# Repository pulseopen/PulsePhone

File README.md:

# PulsePhone — Pulse Modular Phone (DART-MX8M-MINI SoM)

> A modular, open-source smartphone built for repairability, upgradability, and hardware freedom.

Built around the **DART-MX8M-MINI SoM**, PulsePhone uses **Hirose DF40** board-to-board connectors across all subsystems — keeping modules isolated, swappable, and independently developable.

---

## Sponsorship
PulsePhone is proudly sponsored by [PCBWay](https://www.pcbway.com), 
through their project sponsorship program.

---

## System Architecture

The **Main Board** is the hub of the system, hosting the MCM-iMX93 SoM, power management, WiFi/BT, onboard DAC, and all signal routing. Every peripheral connects via DF40 connectors following the MBI-Lite standard.

| Module         | Interface          | Role                                               |
|----------------|--------------------|----------------------------------------------------|
| Main Board     | DF40 (host)        | MCM-iMX93 SoM, WiFi/BT, DAC, power management     |
| Display Module | MIPI-DSI + Touch   | Adapter for wide MIPI-DSI display compatibility    |
| Camera Module  | MIPI CSI-2         | Adapter for wide MIPI-CSI camera compatibility     |
| Audio Module   | Analog             | Amp, speaker, headphone, mic                       |

Full connector pinout in [MBI-Lite Specification](MBI-LITE.md).

---

## Project Goals

- One connector standard (DF40) across every module
- Debian
- Kit-oriented design — bring your own display and case
- Fully open: KiCad source + mechanical files under GNU GPL-V3.0

---

## Hardware Status

### Main Board — Rev 2
- DART-MX8M-MINI
- M.2 WiFi/BT Module.
- PCM5102A audio DAC routed to SAI port
- TPS63020 buck-boost regulator, AP2112K-3.3 LDO
- TP4056 battery charger, MIC2877 5V boost

### Rev 1 — Lessons Learned
- XL1509 EN pin active-low behavior caused 3.3V rail failure (fixed in Rev 2 by switching to AP2112K LDO)
- Test pad size too small for reliable probing (all pads 2mm minimum in Rev 2)
- SoM partial boot activity observed but UART output not confirmed **More on this below*

### Display Module
PCB design complete. Functions as a passive MIPI-DSI adapter for broad display compatibility.

### Camera Module
Design TBD.

### Audio Module
Design in progress.

### Wifi/BT (M.2 Module)
M.2 key e connector which allows for a wide range of consumer wifi solutions.

### Mod Port (NEW DF40 MODULE!)
New connector that allows tinkerers to make their own custom pulsephone modules (ex. custom rfid modules, ir remote module, etc...)! Connector's pinout is stocked with loads of GPIO, UART, and I2C.

---

## Software Target

- **OS:** Debian linux
- **Target:** First Linux boot soon...

---

## First Bringup Summary (Rev 1) *Failed :(*

- First bringup was not a success as boot only got upto flashing light on the SoM.
- Soldering is to be improved upon with planned access to a Uni FabLab.
- I presume the main cause for failure of Rev 1 was poor soldering quality and electrical faults that were not caught before ordering boards.

---

## Current Status

Rev 2 schematic and PCB complete. Pre-order review week in progress before board order. Targeting first Linux boot on Rev 2 hardware.

---

## Documentation

- [MBI-Lite Module Connector Specification](MBI-LITE.md)
- [Contributing](CONTRIBUTING.md)
- [License](LICENSE)

---

## License

Hardware released under **GNU GPL-V3.0**.

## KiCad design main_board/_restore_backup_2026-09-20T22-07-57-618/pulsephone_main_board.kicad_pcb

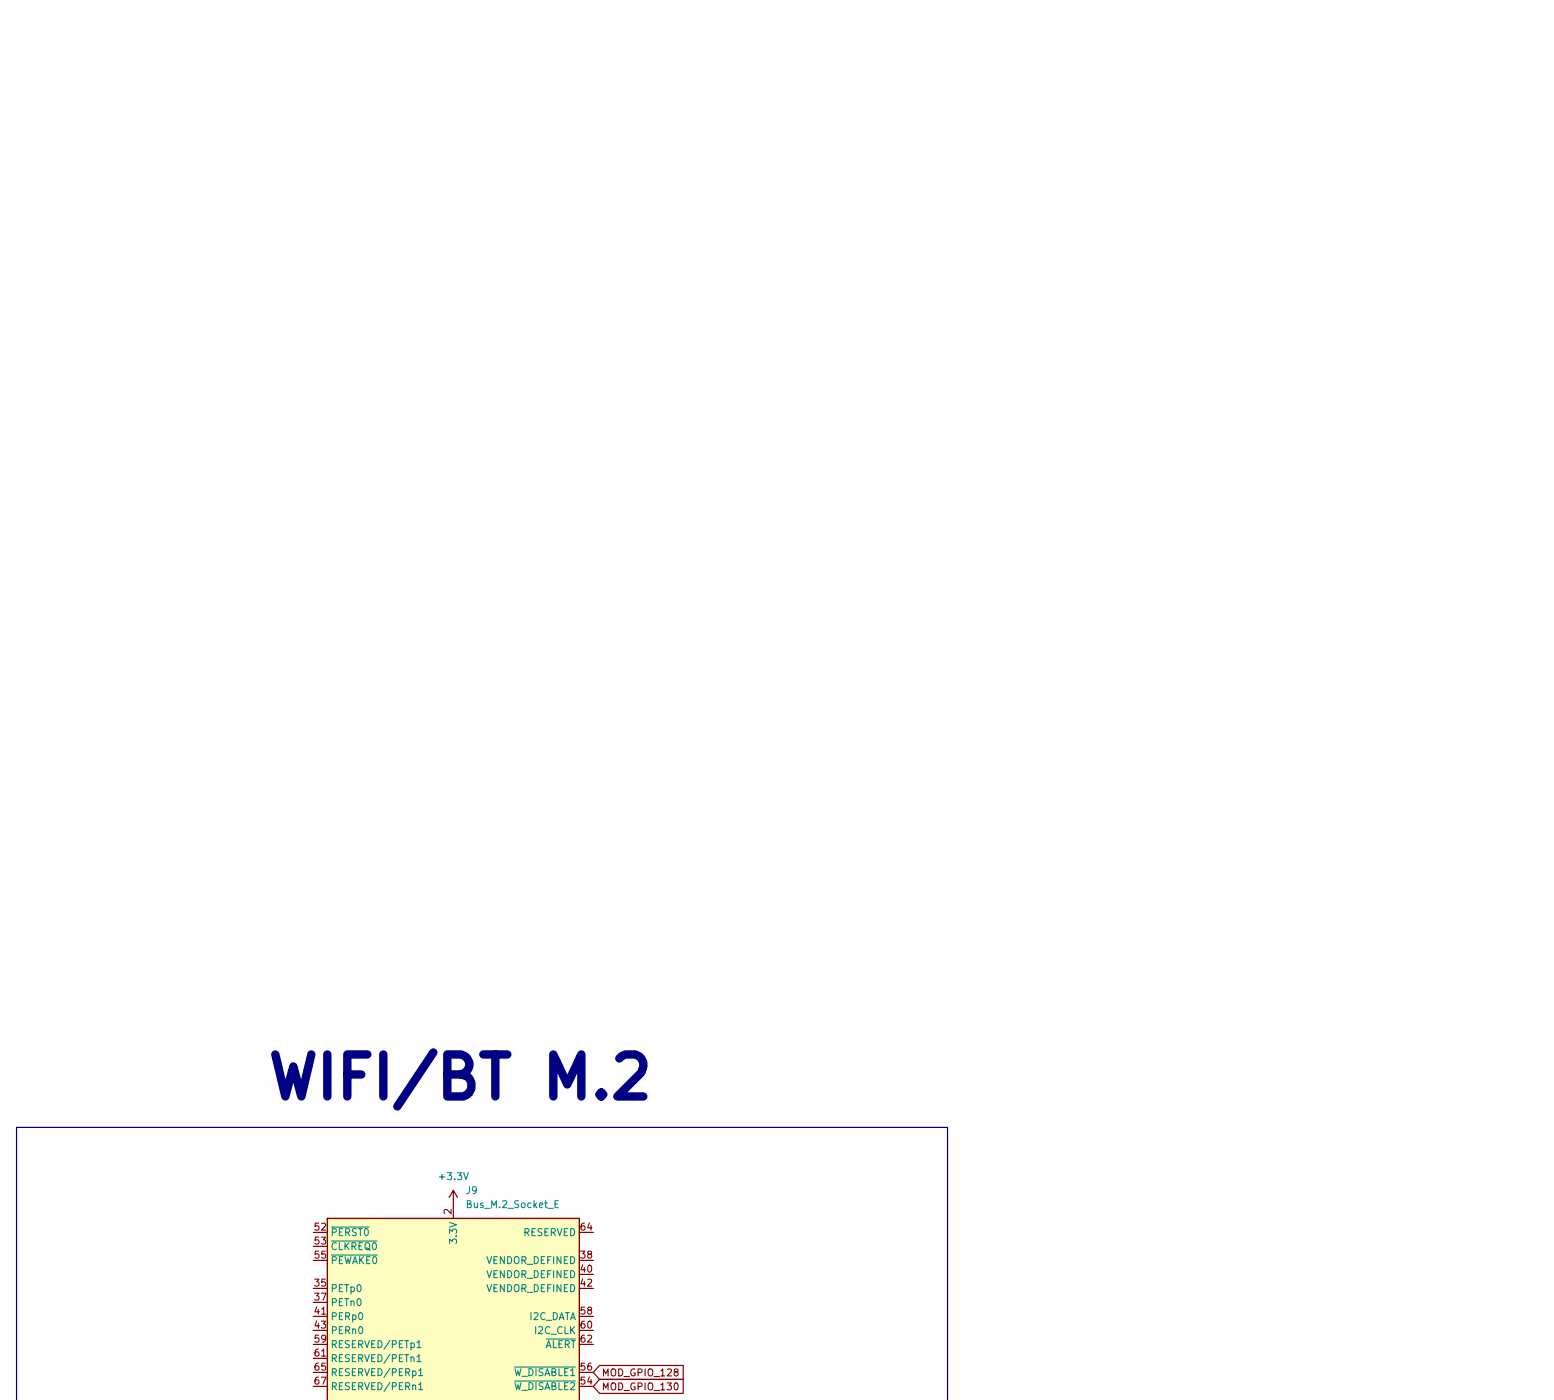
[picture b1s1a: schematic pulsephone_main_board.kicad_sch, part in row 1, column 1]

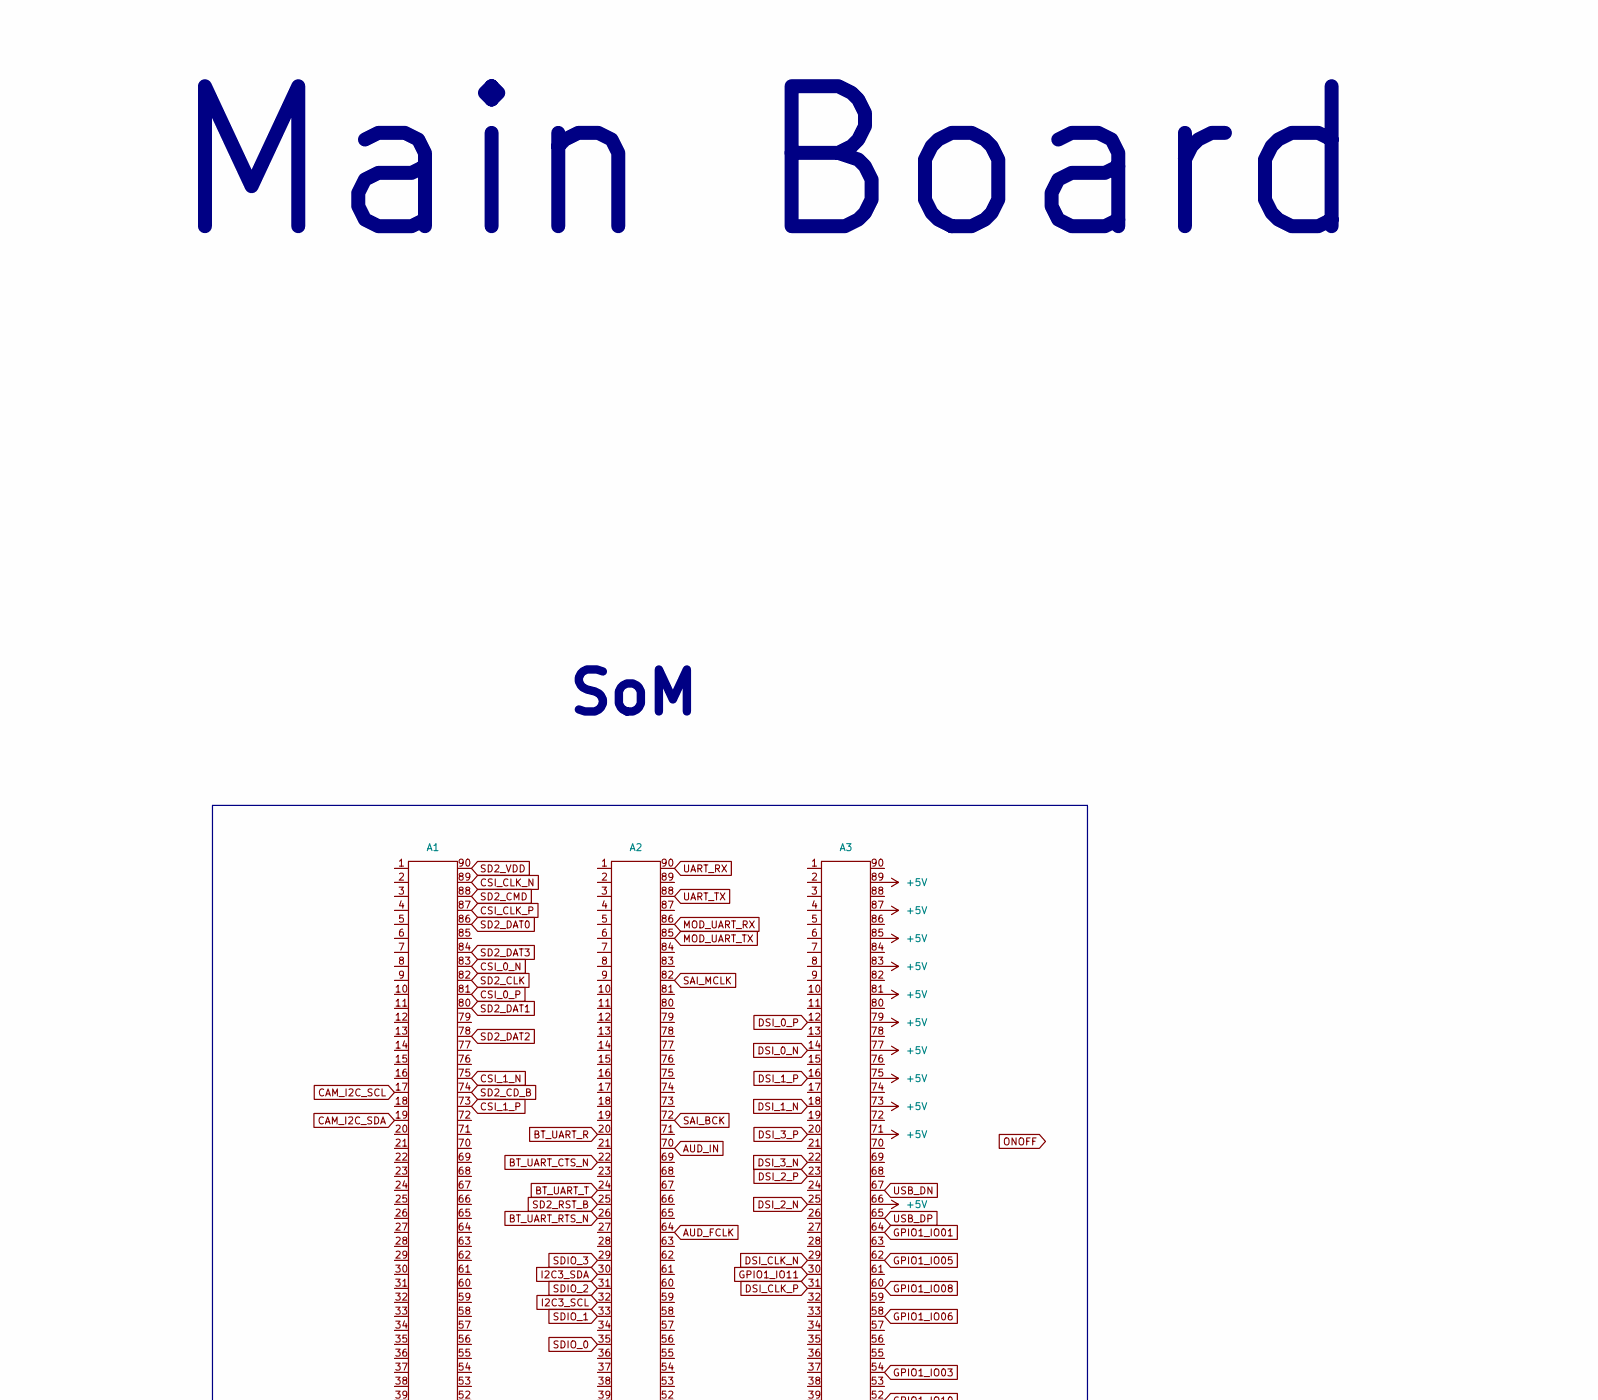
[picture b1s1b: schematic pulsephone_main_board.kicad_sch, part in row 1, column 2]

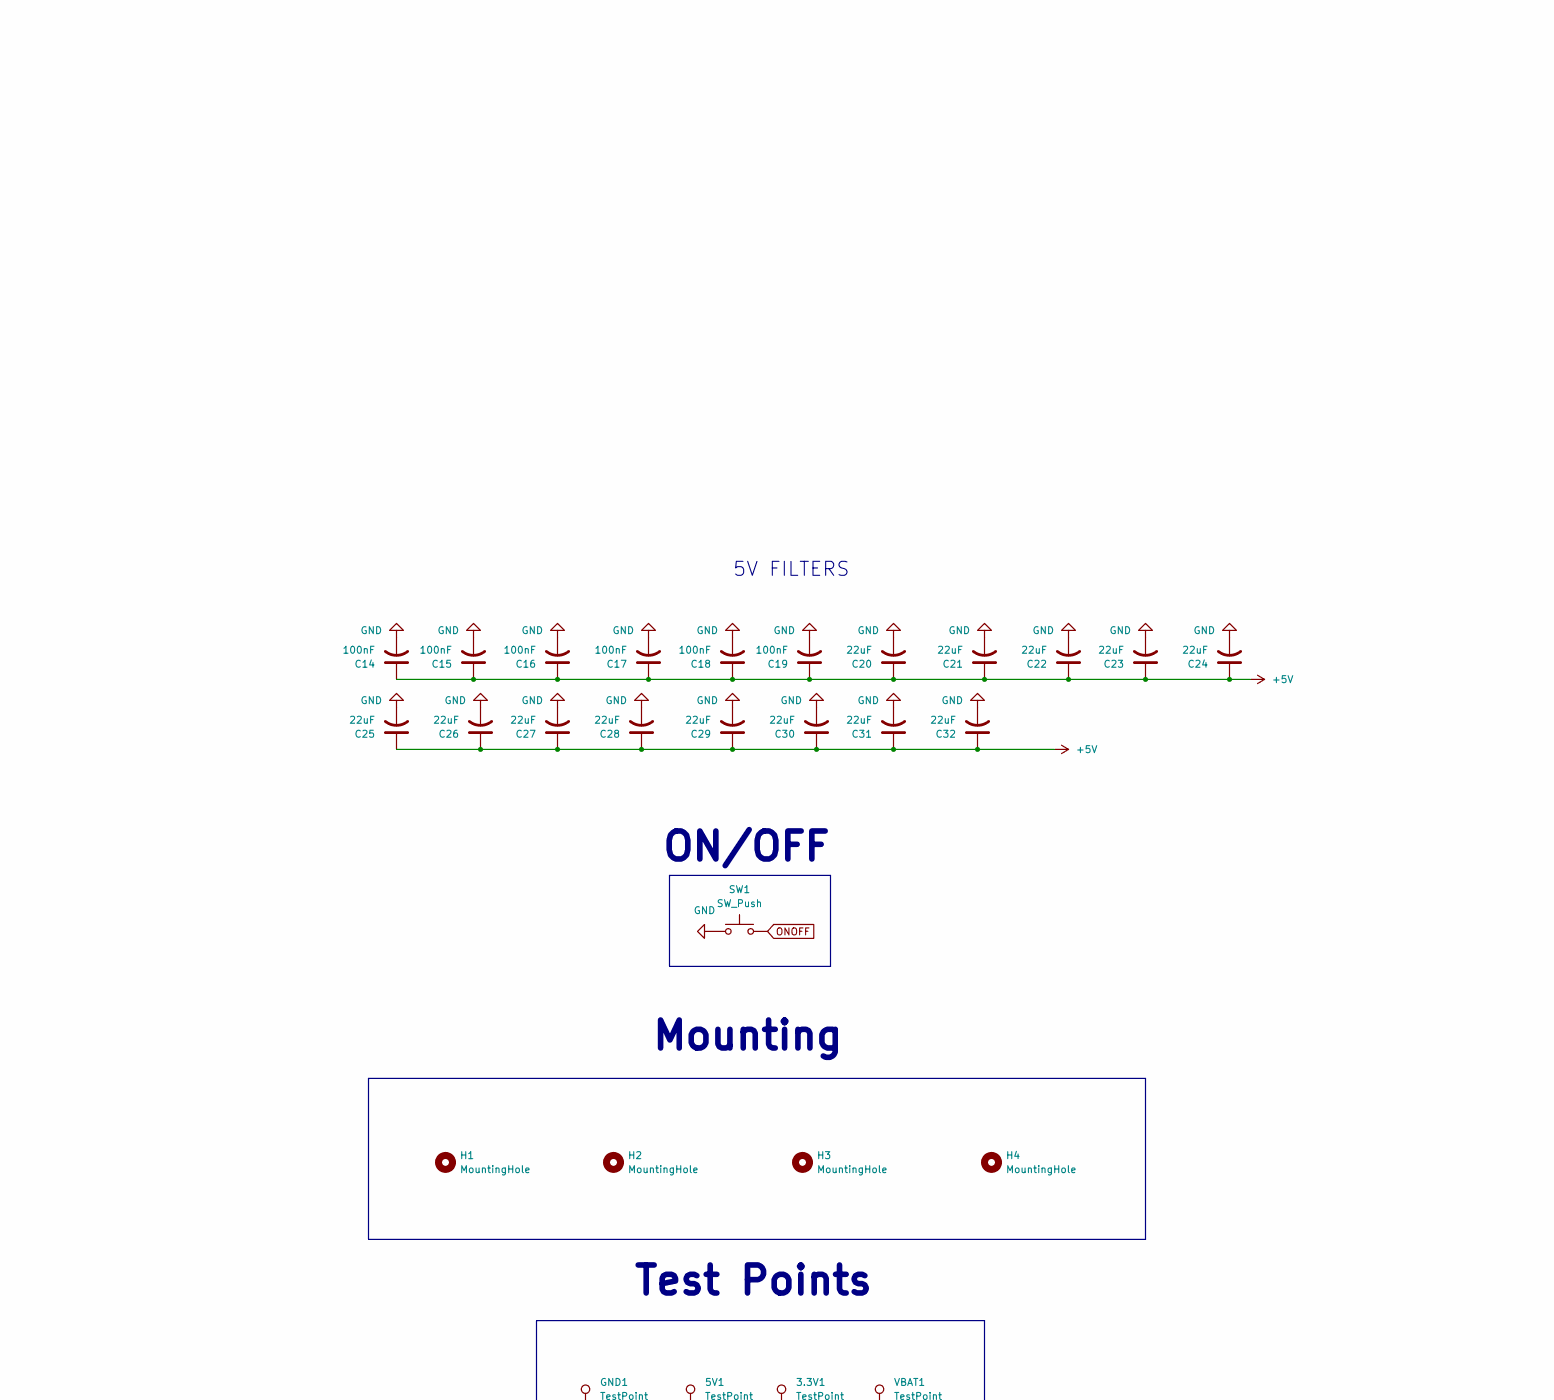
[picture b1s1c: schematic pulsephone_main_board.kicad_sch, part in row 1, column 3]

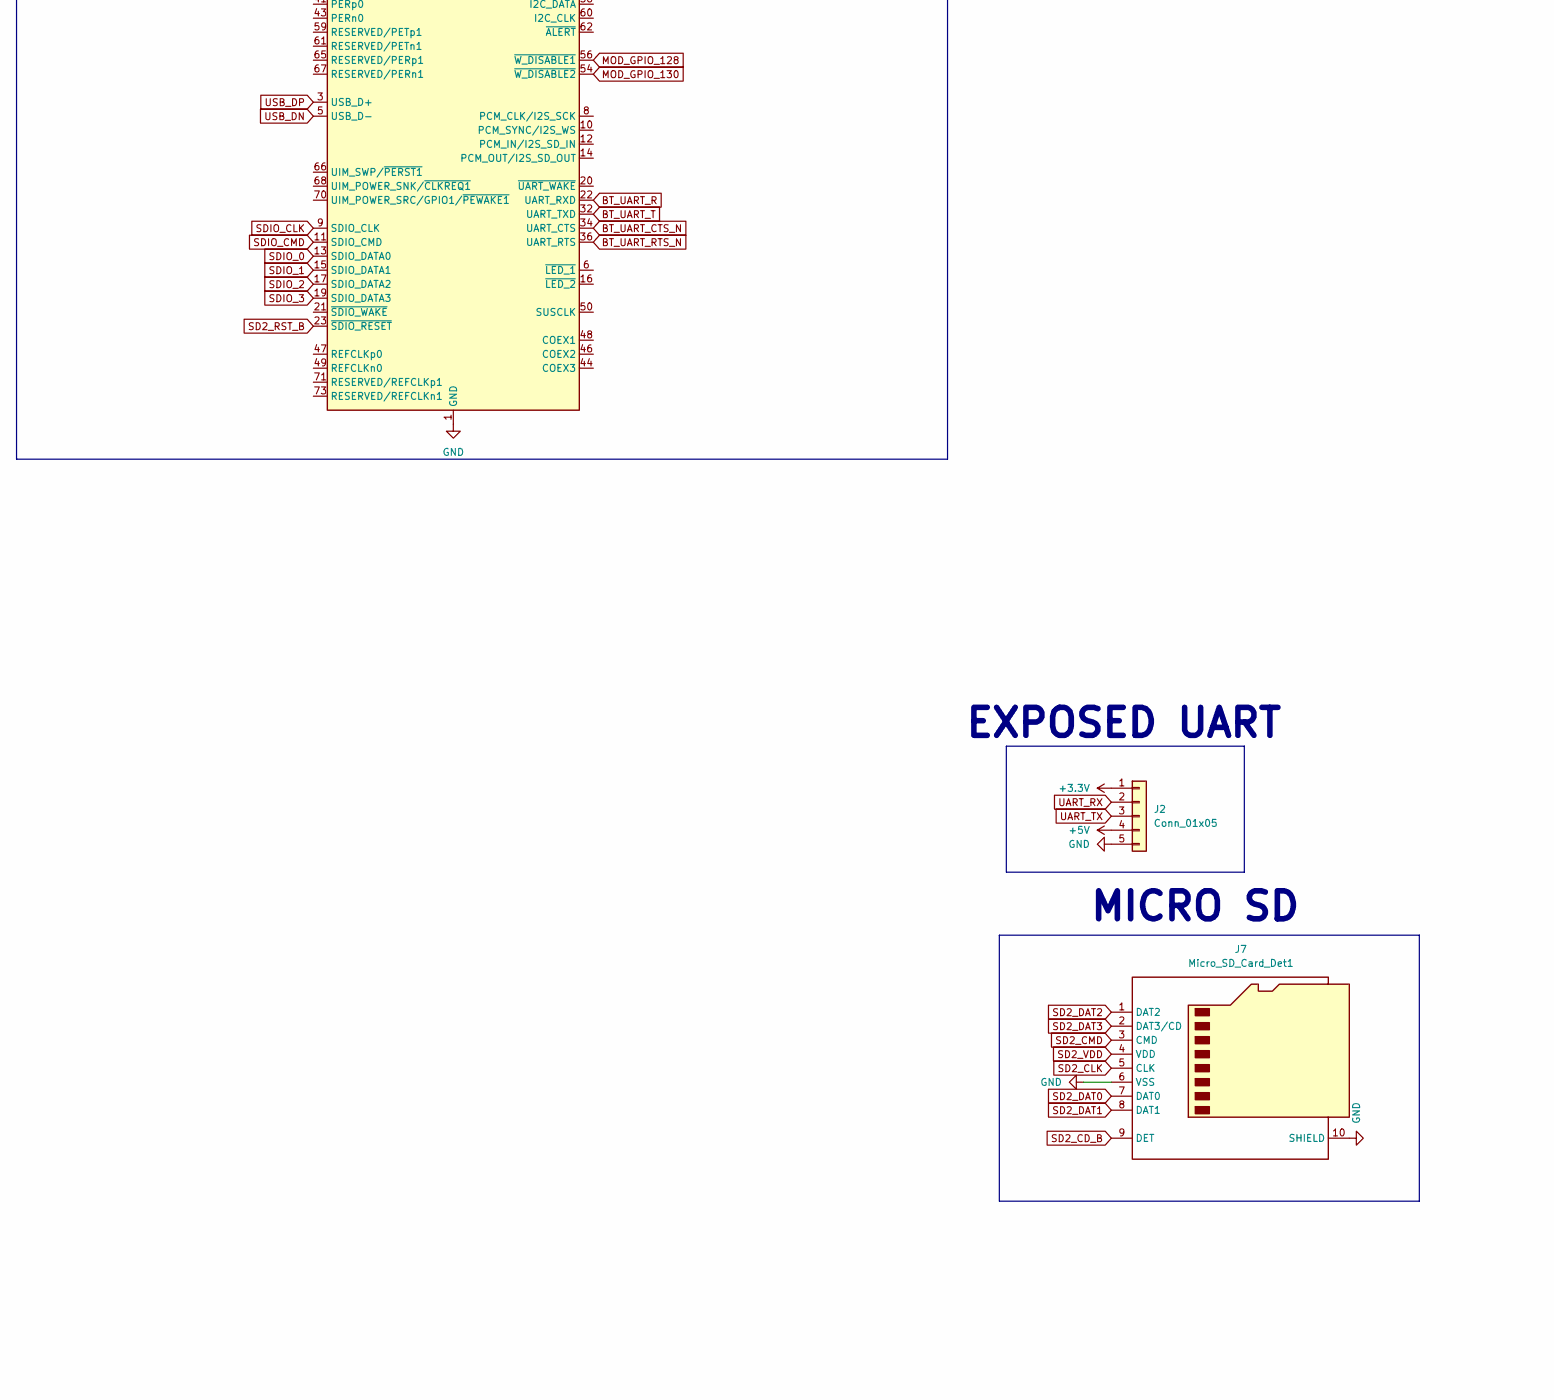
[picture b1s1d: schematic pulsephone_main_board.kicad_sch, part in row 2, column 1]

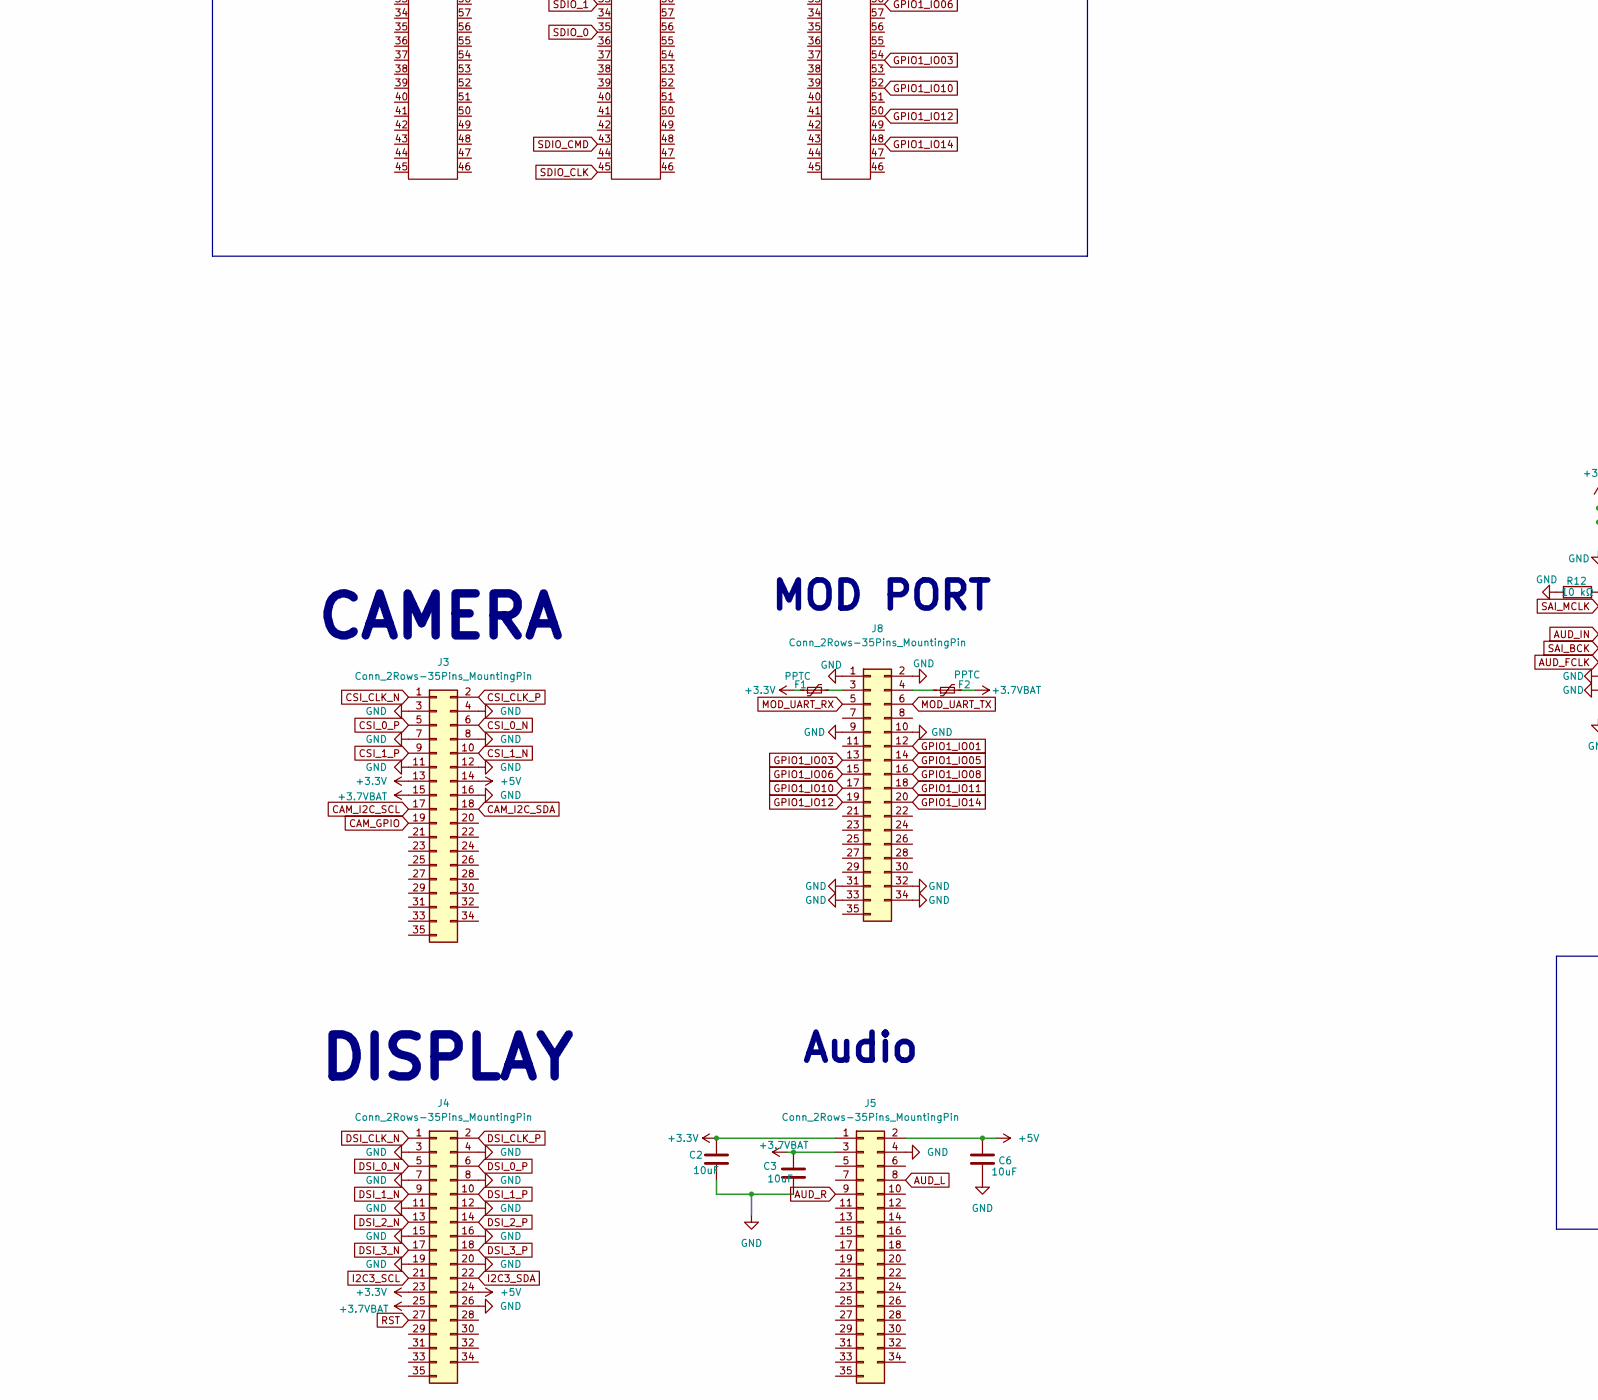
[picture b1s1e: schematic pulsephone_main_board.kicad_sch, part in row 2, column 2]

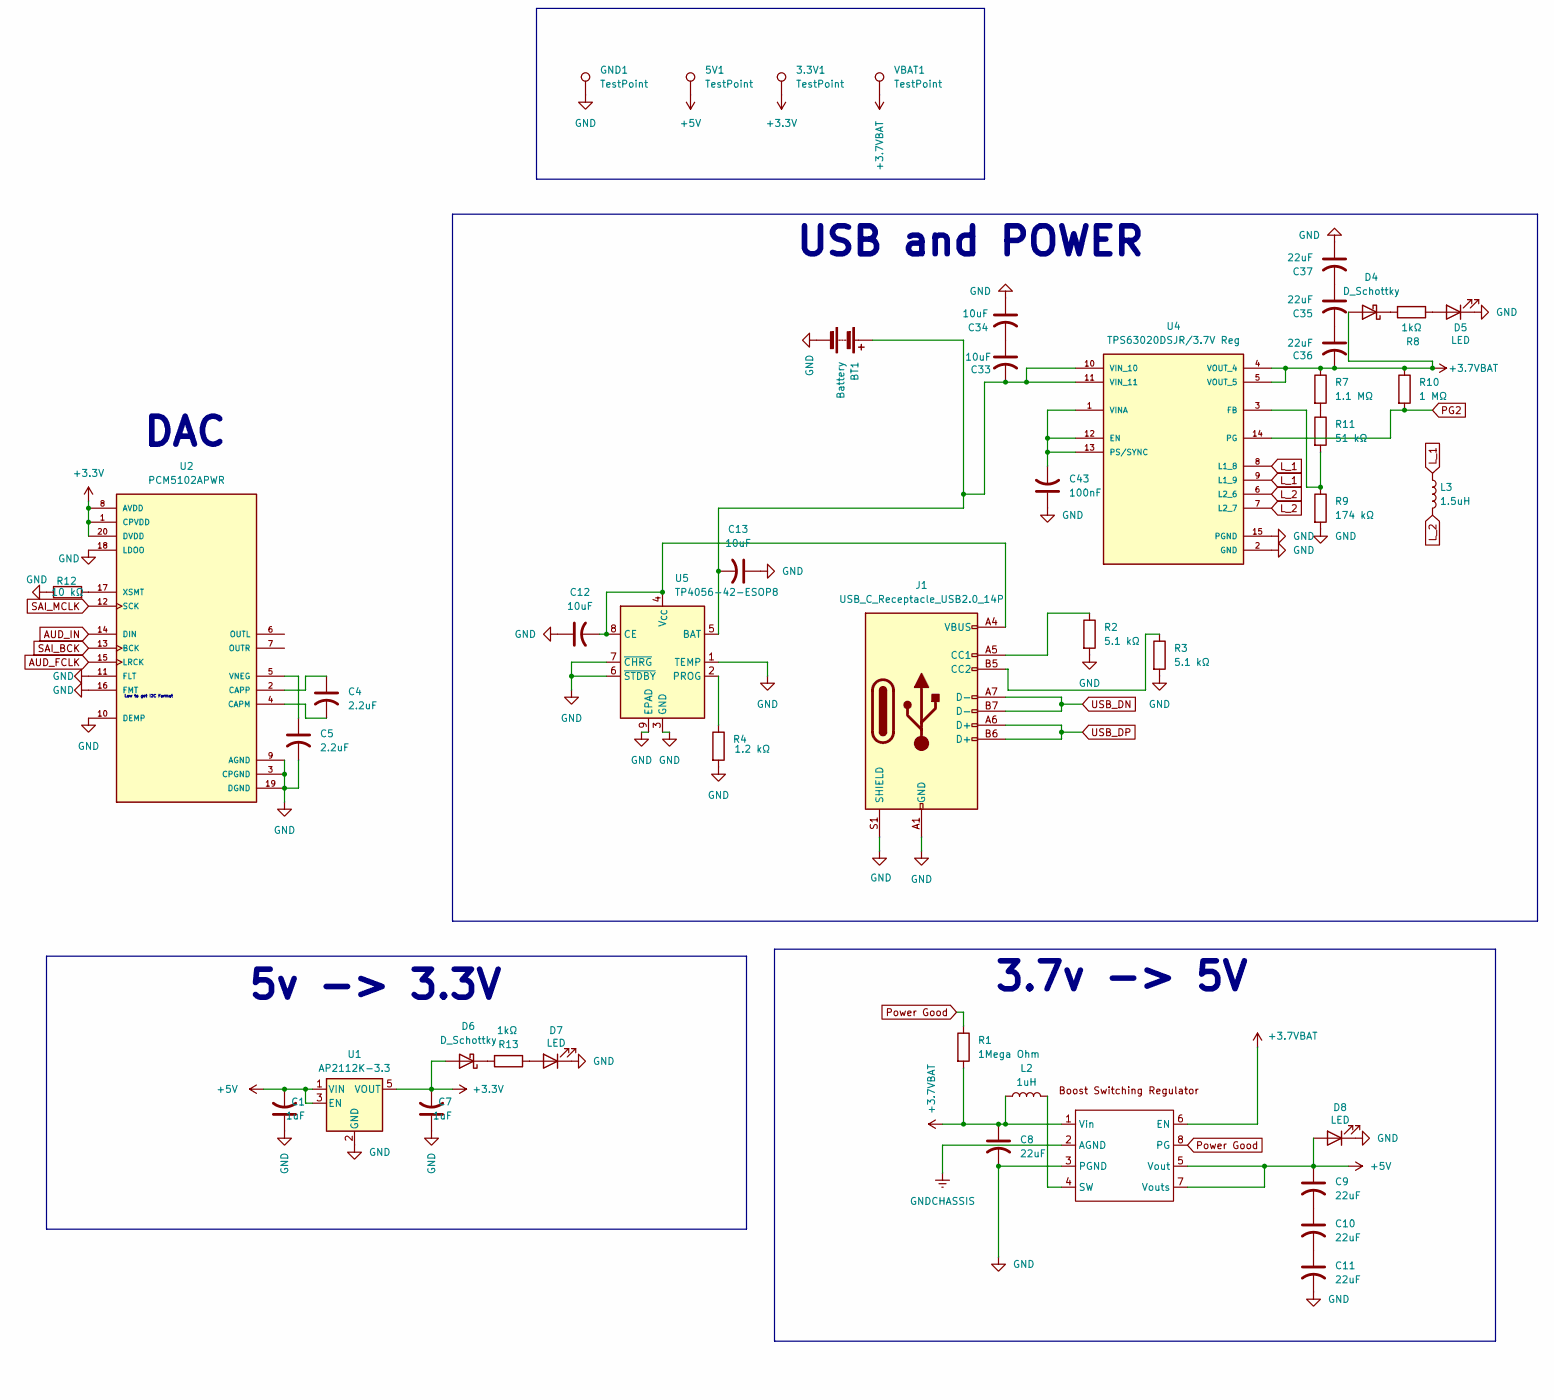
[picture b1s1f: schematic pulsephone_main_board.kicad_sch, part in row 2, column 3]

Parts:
3.3V1, 5V1: TestPoint; TestPoint_Pad_D2.5mm
A1, A2, A3: Hirose_DF40C-90DS-0.4V_2x45_P0.4mm
BT1: Battery; PinHeader_1x02_P2.54mm_Horizontal
C1, C7: 1uF; C_0603_1608Metric
C2, C3, C6, C12, C13, C33, C34: 10uF; C_0603_1608Metric
C4, C5: 2.2uF; C_0603_1608Metric
C8, C9, C10, C11, C20, C21, C22, C23, C24, C25, C26, C27, C28, C29, C30, C31, C32, C35, C36, C37: 22uF; C_0805_2012Metric
C14, C15, C16, C17, C18, C19: 100nF; C_0805_2012Metric
C43: 100nF; C_0603_1608Metric
D4, D6: D_Schottky; D_SMA
D5, D7, D8: LED; LED_0805_2012Metric
F1, F2: PPTC; R_0805_2012Metric
GND1: TestPoint; TestPoint_Pad_D2.5mm
H1, H2, H3, H4: MountingHole; MountingHole_2.2mm_M2_DIN965_Pad
J1: USB_C_Receptacle_USB2.0_14P; USB_C_Receptacle_HRO_TYPE-C-31-M-12
J2: Conn_01x05; PinHeader_1x05_P2.54mm_Horizontal
J3, J4, J5, J8: Conn_2Rows-35Pins_MountingPin; HIROSE_DF40C-34DS-0.4V_58_
J7: Micro_SD_Card_Det1; microSD_HC_Hirose_DM3AT-SF-PEJM5
J9: Bus_M.2_Socket_E; AMPHENOL_MDT180E03001
L2: 1uH; L_Wurth_WE-LQSH-4020
L3: 1.5uH; L_Wurth_WE-LQSH-4020
R1: 1Mega Ohm; R_0603_1608Metric_Pad0.98x0.95mm_HandSolder
R2, R3: 5.1 kΩ; R_0805_2012Metric
R4: 1.2 kΩ; R_0805_2012Metric
R7: 1.1 MΩ; R_0805_2012Metric
R8, R13: 1kΩ; R_0805_2012Metric
R9: 174 kΩ; R_0805_2012Metric
R10: 1 MΩ; R_0805_2012Metric
R11: 51 kΩ; R_0805_2012Metric
R12: 10 kΩ; R_0805_2012Metric
SW1: SW_Push
U1: AP2112K-3.3; SOT-23-5
U2: PCM5102APWR; SOP65P640X120-20N; PARTREV C
U3: VREG_MIC2877-AYFT-TR
U4: TPS63020DSJR/3.7V Reg; IC_TPS63020DSJR
U5: TP4056-42-ESOP8; SOIC-8-1EP_3.9x4.9mm_P1.27mm_EP2.41x3.3mm_ThermalVias
VBAT1: TestPoint; TestPoint_Pad_D2.5mm

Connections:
+3.3V: 3.3V1.1 (1_1), C2.1, C7.2, D6.2 (A), F1.1, J2.1, J3.13, J4.23, J5.1, J9.2 (3.3V), J9.4 (3.3V), J9.72 (3.3V), J9.74 (3.3V), U1.5 (VOUT), U2.1 (CPVDD), U2.8 (AVDD), U2.20 (DVDD)
+3.7VBAT: C3.1, C8.1, C36.2, D4.2 (A), F2.2, J3.15, J4.25, J5.3, L2.1, R1.2, R7.1, R10.1, U3.1 (Vin), U3.6 (EN), U4.4 (VOUT_4), U4.5 (VOUT_5), VBAT1.1 (1_1)
+5V: 5V1.1 (1_1), A3.66, A3.71, A3.73, A3.75, A3.77, A3.79, A3.81, A3.83, A3.85, A3.87, A3.89, C1.2, C6.1, C9.1, C14.1, C15.1, C16.1, C17.1, C18.1, C19.1, C20.1, C21.1, C22.1, C23.1, C24.1, C25.1, C26.1, C27.1, C28.1, C29.1, C30.1, C31.1, C32.1, D8.2 (A), J2.4, J3.14, J4.24, J5.2, U1.1 (VIN), U1.3 (EN), U3.5 (Vout), U3.7 (Vouts)
AUD_FCLK: A2.64, U2.15 (LRCK)
AUD_IN: A2.70, U2.14 (DIN)
AUD_L: J5.8
AUD_R: J5.9
BT_UART_CTS_N: A2.22, J9.34 (UART_CTS)
BT_UART_R: A2.20, J9.22 (UART_RXD)
BT_UART_RTS_N: A2.26, J9.36 (UART_RTS)
BT_UART_T: A2.24, J9.32 (UART_TXD)
CAM_GPIO: J3.19
CAM_I2C_SCL: A1.17, J3.17
CAM_I2C_SDA: A1.19, J3.18
CSI_0_N: A1.83, J3.6
CSI_0_P: A1.81, J3.5
CSI_1_N: A1.75, J3.10
CSI_1_P: A1.73, J3.9
CSI_CLK_N: A1.89, J3.1
CSI_CLK_P: A1.87, J3.2
DSI_0_N: A3.14, J4.5
DSI_0_P: A3.12, J4.6
DSI_1_N: A3.18, J4.9
DSI_1_P: A3.16, J4.10
DSI_2_N: A3.25, J4.13
DSI_2_P: A3.23, J4.14
DSI_3_N: A3.22, J4.17
DSI_3_P: A3.20, J4.18
DSI_CLK_N: A3.29, J4.1
DSI_CLK_P: A3.31, J4.2
GND: BT1.2 (-), C1.1, C2.2, C3.2, C5.2, C6.2, C7.1, C8.2, C11.2, C12.1, C13.1, C14.2, C15.2, C16.2, C17.2, C18.2, C19.2, C20.2, C21.2, C22.2, C23.2, C24.2, C25.2, C26.2, C27.2, C28.2, C29.2, C30.2, C31.2, C32.2, C34.1, C37.1, C43.1, D5.1 (K), D7.1 (K), D8.1 (K), GND1.1 (1_1), J1.A1 (GND), J1.A12 (GND), J1.B1 (GND), J1.B12 (GND), J1.S1 (SHIELD), J2.5, J3.3, J3.4, J3.7, J3.8, J3.11, J3.12, J3.16, J4.3, J4.4, J4.7, J4.8, J4.11, J4.12, J4.15, J4.16, J4.19, J4.20, J4.26, J5.4, J7.6 (VSS), J7.10 (SHIELD), J8.1, J8.2, J8.9, J8.10, J8.31, J8.32, J8.33, J8.34, J9.1 (GND), J9.7 (GND), J9.18 (GND), J9.33 (GND), J9.39 (GND), J9.45 (GND), J9.51 (GND), J9.57 (GND), J9.63 (GND), J9.69 (GND), J9.75 (GND), R2.2, R3.2, R4.2, R9.2, R12.1, SW1.1, U1.2 (GND), U2.3 (CPGND), U2.9 (AGND), U2.10 (DEMP), U2.11 (FLT), U2.16 (FMT), U2.18 (LDOO), U2.19 (DGND), U3.3 (PGND), U4.2 (GND), U4.15 (PGND), U5.1 (TEMP), U5.3 (GND), U5.6 (~STDBY), U5.7 (~CHRG), U5.9 (EPAD)
GNDCHASSIS: U3.2 (AGND)
GPIO1_IO01: A3.64, J8.12
GPIO1_IO03: A3.54, J8.13
GPIO1_IO05: A3.62, J8.14
GPIO1_IO06: A3.58, J8.15
GPIO1_IO08: A3.60, J8.16
GPIO1_IO10: A3.52, J8.17
GPIO1_IO11: A3.30, J8.18
GPIO1_IO12: A3.50, J8.19
GPIO1_IO14: A3.48, J8.20
I2C3_SCL: A2.32, J4.21
I2C3_SDA: A2.30, J4.22
L_1: L3.1, U4.8 (L1_8), U4.9 (L1_9)
L_2: L3.2, U4.6 (L2_6), U4.7 (L2_7)
MOD_GPIO_128: J9.56 (~W_DISABLE1)
MOD_GPIO_130: J9.54 (~W_DISABLE2)
MOD_UART_RX: A2.86, J8.5
MOD_UART_TX: A2.85, J8.6
unnamed: BT1.1 (+), C13.2, C33.2, U4.10 (VIN_10), U4.11 (VIN_11), U5.5 (BAT)
unnamed: C9.2, C10.1
unnamed: C10.2, C11.1
unnamed: C33.1, C34.2
unnamed: C35.1, C37.2
unnamed: C35.2, C36.1
unnamed: D4.1 (K), R8.2
unnamed: D5.2 (A), R8.1
unnamed: D6.1 (K), R13.2
unnamed: D7.2 (A), R13.1
unnamed: J1.A5 (CC1), R2.1
unnamed: J1.B5 (CC2), R3.1
unnamed: F1.2, J8.3
unnamed: F2.1, J8.4
unnamed: R7.2, R11.1
unnamed: C4.2, U2.4 (CAPM)
unnamed: C4.1, U2.2 (CAPP)
unnamed: C5.1, U2.5 (VNEG)
unnamed: R12.2, U2.17 (XSMT)
unnamed: L2.2, U3.4 (SW)
unnamed: C43.2, U4.1 (VINA), U4.12 (EN), U4.13 (PS/SYNC)
unnamed: R9.1, R11.2, U4.3 (FB)
unnamed: C12.2, J1.A4 (VBUS), J1.A9 (VBUS), J1.B4 (VBUS), J1.B9 (VBUS), U5.4 (V_{CC}), U5.8 (CE)
unnamed: R4.1, U5.2 (PROG)
PG2: R10.2, U4.14 (PG)
Power Good: R1.1, U3.8 (PG)
RST: J4.27
SAI_BCK: A2.72, U2.13 (BCK)
SAI_MCLK: A2.82, U2.12 (SCK)
SD2_CD_B: A1.74, J7.9 (DET)
SD2_CLK: A1.82, J7.5 (CLK)
SD2_CMD: A1.88, J7.3 (CMD)
SD2_DAT0: A1.86, J7.7 (DAT0)
SD2_DAT1: A1.80, J7.8 (DAT1)
SD2_DAT2: A1.78, J7.1 (DAT2)
SD2_DAT3: A1.84, J7.2 (DAT3/CD)
SD2_RST_B: A2.25, J9.23 (~SDIO_RESET)
SD2_VDD: A1.90, J7.4 (VDD)
SDIO_0: A2.35, J9.13 (SDIO_DATA0)
SDIO_1: A2.33, J9.15 (SDIO_DATA1)
SDIO_2: A2.31, J9.17 (SDIO_DATA2)
SDIO_3: A2.29, J9.19 (SDIO_DATA3)
SDIO_CLK: A2.45, J9.9 (SDIO_CLK)
SDIO_CMD: A2.43, J9.11 (SDIO_CMD)
UART_RX: A2.90, J2.2
UART_TX: A2.88, J2.3
USB_DN: A3.67, J1.A7 (D-), J1.B7 (D-), J9.5 (USB_D-)
USB_DP: A3.65, J1.A6 (D+), J1.B6 (D+), J9.3 (USB_D+)

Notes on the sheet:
3.7v -> 5V
DAC
Main Board
SoM
MOD PORT
5v -> 3.3V
5V FILTERS
USB and POWER
Audio
Low to get I2C Format
Mounting
ON/OFF
DISPLAY
EXPOSED UART
Test Points
MICRO SD
WIFI/BT M.2
CAMERA

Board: 4 copper layers, 84 parts (0 on the bottom side), 90 nets, no tracks yet.

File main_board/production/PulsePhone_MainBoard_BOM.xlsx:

Line# | Ref Des | Qty | Value / Description | Package/Footprint | MPN | Manufacturer | Distributor Stock Check | Sourcing Notes / Flags
1 | A1, A2, A3 | 3 | Board-to-board receptacle, SoM connector | DF40C-90DS-0.4V 2x45 0.4mm | DF40C-90DS-0.4V(51) | Hirose | DigiKey H11877CT-ND, in stock | Stack-height suffix (51)/(54)/(58) sets mated height — confirm against the DART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
2 | BT1 | 1 | 2-pin battery header, 2.54mm | PinHeader 1x02 2.54mm | 22-23-2021 | Molex | DigiKey WM4200-ND, in stock | Generic 2.54mm header, drop-in.
3 | C1, C7 | 2 | 1uF | 0603 | CL10A105KP8NNNC | Samsung Electro-Mechanics | DigiKey 1276-1000-1-ND, in stock | X5R 16V, common.
4 | C2, C3, C6, C13, C33, C12, (+1 more) | 7 | 10uF | 0603 | CL10A106MQ8NRNC | Samsung Electro-Mechanics | DigiKey 1276-1023-1-ND, in stock | X5R 10V, 0603 10uF is a tight squeeze — confirm DC-bias derating at your rail v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
5 | C14, C15, C16, C17, C18, C19 | 6 | 100nF | 0805 | CL21B104KBCNNNC | Samsung Electro-Mechanics | DigiKey 1276-1000-2-ND-class, in stock | X7R 50V decoupling, standard.
6 | C8, C22, C24, C30, C35, C37 (+14 more) | 20 | 22uF | 0805 | CL21A226MQQNNNE | Samsung Electro-Mechanics | DigiKey 1276-3329-1-ND, in stock | X5R 6.3V — check this is >= your actual rail (VBAT domain hits 4.57V per the po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
7 | C4, C5 | 2 | 2.2uF | 0603 | CL10A225KP8NNNC | Samsung Electro-Mechanics | DigiKey 1276-1006-1-ND, in stock | X5R 16V.
8 | C43 | 1 | 100nF | 0603 | CL10B104KB8NNNC | Samsung Electro-Mechanics | DigiKey 1276-1122-1-ND, in stock | X7R 50V.
9 | D4, D6 | 2 | Schottky diode | SMA | SS34 | various (Yangzhou Yangjie / Comchip / Diodes Inc CMSH3-40) | DigiKey / LCSC, in stock (SS34 or CMSH3-40MA) | 3A/40V SMA Schottky — confirm current/reverse-voltage against the actual protec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
10 | D5, D7, D8 | 3 | LED | 0805 | LTST-C171KFKT | Lite-On | DigiKey 160-1446-1-ND, in stock | Red 0805 — swap color/MPN per actual indicator function (charge/power/status).
11 | F1, F2 | 2 | PPTC resettable fuse | 0805 | MICROSMD050F-2 | Bourns | DigiKey Bourns Inc.-ND, in stock | 0.5A hold — verify trip current matches your actual VBUS/rail current budget.
12 | GND1, 3.3V1, VBAT1, 5V1 | 4 | Test point, 2.5mm pad | TestPoint_Pad_D2.5mm | 5010 | Keystone Electronics | DigiKey 36-5010-ND, in stock | Standard bare test point loop/pad — no real fine MPN needed, often left DNP for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
13 | J1 | 1 | USB-C receptacle, 2.0 14-pin, mid-mount | TYPE-C-31-M-12 | TYPE-C-31-M-12 | HRO / Korean Hroparts Elec | LCSC C165948, in stock. NOT listed on DigiKey/Mouser. | Real sourcing gap: this exact HRO part is an LCSC/JLCPCB-catalog commodity conn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
14 | J2 | 1 | 5-pin header, 2.54mm | PinHeader 1x05 2.54mm | 22-23-2051 | Molex | DigiKey WM4204-ND, in stock | Generic.
15 | J3, J4, J5, J8 | 4 | Board-to-board receptacle, 34-pin | DF40C-34DS-0.4V(58) | DF40C-34DS-0.4V(58) | Hirose | DigiKey H124600TR-ND, in stock | Footprint already specifies the (58) stack height — confirmed orderable.
16 | J7 | 1 | microSD card socket, push-push | DM3AT-SF-PEJM5 | DM3AT-SF-PEJM5(11) | Hirose | DigiKey, in stock (multiple suffix variants — confirm (11) vs bare vs (40)) | Bare DM3AT-SF-PEJM5 and several numbered suffixes (11)/(40) all show as distinc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
17 | J9 | 1 | M.2 Key-E socket, 0.5mm, 3.0H | AMPHENOL_MDT180E03001 | MDT180E03001 | Amphenol ICC (FCI) | DigiKey MDT180E03001CT-ND, in stock | Confirmed exact match.
18 | L2 | 1 | 1uH shielded power inductor | WE-LQSH 4020 | 74405042010 | Wurth Elektronik | DigiKey 732-74405042010-ND, in stock | Matches footprint exactly.
19 | L3 | 1 | 1.5uH shielded power inductor | WE-LQSH 4020 | 74405042015 | Wurth Elektronik | DigiKey 732-74405042015-ND, in stock | Matches footprint exactly.
20 | R1 | 1 | 1MOhm | 0603 | RC0603FR-071ML | Yageo | DigiKey 311-1.00MHRCT-ND, in stock
21 | R5 | 1 | 10kOhm (NEW — not in prior schematic BOM) | 0603 | RC0603FR-0710KL | Yageo | DigiKey 311-10.0KHRCT-ND, in stock | FLAG: R5 exists on this new PCB revision but was absent from the last schematic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
22 | R10 | 1 | 1MOhm | 0805 | RC0805FR-071ML | Yageo | DigiKey 311-1.00MCRCT-ND, in stock
23 | R11 | 1 | 51kOhm | 0805 | RC0805FR-0751KL | Yageo | DigiKey 311-51.0KCRCT-ND, in stock
24 | R12 | 1 | 10kOhm | 0805 | RC0805FR-0710KL | Yageo | DigiKey 311-10.0KCRCT-ND, in stock
25 | R13, R8 | 2 | 1kOhm | 0805 | RC0805FR-071KL | Yageo | DigiKey 311-1.00KCRCT-ND, in stock
26 | R2, R3 | 2 | 5.1kOhm | 0805 | RC0805FR-075K1L | Yageo | DigiKey 311-5.10KCRCT-ND, in stock
27 | R4 | 1 | 1.2kOhm | 0805 | RC0805FR-071K2L | Yageo | DigiKey 311-1.20KCRCT-ND, in stock
28 | R7 | 1 | 1.1MOhm | 0805 | RC0805FR-071M1L | Yageo | DigiKey 311-1.10MCRCT-ND, in stock
29 | R9 | 1 | 174kOhm | 0805 | RC0805FR-07174KL | Yageo | DigiKey 311-174KCRCT-ND, in stock | 1% — used in a feedback/sense divider per the schematic; do not substitute a 5%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
30 | SW1 | 1 | Tactile switch, side-actuated | EVQ-P7A01P | EVQ-P7A01P | Panasonic | DigiKey, in stock | Confirmed exact match.
31 | U1 | 1 | +3.3V LDO, 600mA | SOT-23-5 | AP2112K-3.3TRG1 | Diodes Incorporated | DigiKey AP2112K-3.3TRG1DICT-ND, in stock | Confirmed exact match.
32 | U2 | 1 | Stereo audio DAC | SOP65P640X120-20N (TSSOP-20) | PCM5102APWR | Texas Instruments | DigiKey 296-40348-1-ND, in stock, but TI lead times on this part have run long 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 | Confirmed exact match.
33 | U3 | 1 | +5V synchronous boost regulator | VREG_MIC2877-AYFT-TR (SOT-23-6ish) | MIC2877-5.0YFT-TR | Microchip | DigiKey MIC2877-5.0YFT-CT-ND, in stock | Per the schematic file this is U3 (5V rail), not U4 — the footprint library is 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
34 | U4 | 1 | 3.7V buck-boost regulator (battery rail) | IC_TPS63020DSJR (QFN-14) | TPS63020DSJR | Texas Instruments | DigiKey TPS63020DSJR-ND, in stock | Value field and footprint library both say TPS63020DSJR — this is U4 per the sc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
35 | U5 | 1 | Li-ion linear charger, 1A | SOIC-8-1EP_3.9x4.9mm | TP4056-42-ESOP8 | unbranded/multi-source (originally Nanjing Top Power ASIC Corp) | LCSC only for the literal TP4056; NOT on DigiKey or Mouser under any real manuf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 | Real sourcing risk, the biggest one on this board: 'TP4056' is a genericized pa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

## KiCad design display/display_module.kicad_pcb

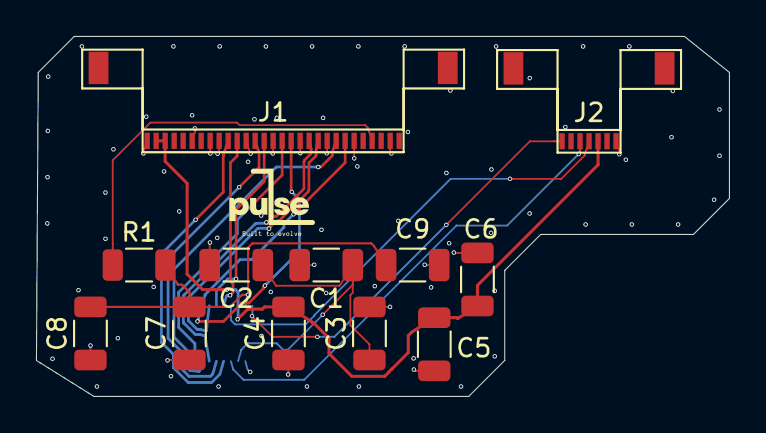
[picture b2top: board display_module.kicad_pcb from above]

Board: 4 copper layers, 38.5 x 20.0 mm, 13 parts (1 on the bottom side), 18 nets.

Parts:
C1, C2, C3, C4, C5, C6, C7, C8, C9: 20uF; C_1206_3216Metric
J1: THD THD0515-29CL-SN; FPC-29-P0.5
J2: FPC LOGIC; FPC_7
J4: DF40; Hirose_DF40C-34DS-0.4V_2x17_P0.4mm
R1: 100 OHM; R_1206_3216Metric

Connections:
+3.3V: C4.2, C5.2, C6.2, J1.27, J1.28, J2.3, J4.13
+3.7VBAT: C7.2, C8.2, C9.2, J4.15, R1.2
+5V: C1.1, C2.1, C3.1, J4.14
DSI-0-N: J1.7, J4.3
DSI-0-P: J1.8, J4.4
DSI-1-N: J1.10, J4.5
DSI-1-P: J1.11, J4.6
DSI-2-N: J1.16, J4.7
DSI-2-P: J1.17, J4.8
DSI-3-N: J1.19, J4.9
DSI-3-P: J1.20, J4.10
DSI-CLK-N: J1.13, J4.1
DSI-CLK-P: J1.14, J4.2
GND: C1.2, C2.2, C3.2, C4.1, C5.1, C6.1, C7.1, C8.1, C9.1, J1.2, J1.6, J1.9, J1.12, J1.15, J1.18, J1.21, J1.22, J1.24, J1.29, J2.1, J4.16
I2C3-SCL: J2.4, J4.11
I2C3-SDA: J2.5, J4.12
unnamed: J1.4, R1.1
RST: J2.7, J4.17

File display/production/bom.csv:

Designator,Footprint,Quantity,Value,LCSC Part #
"C1, C2, C3, C4, C5, C6, C7, C8, C9",1206,9,20uF,
J1,Amphenol_F32R-1A7x1-11029_1x29-1MP_P0.5mm_Horizontal,1,DISPLAY FPC,
J2,Amphenol_F32Q-1A7x1-11007_1x07-1MP_P0.5mm_Horizontal,1,FPC LOGIC,
J4,Hirose_DF40C(2.0)-70DS-0.4V_2x35_P0.4mm,1,DF40,
R1,1206,1,100 OHM,
